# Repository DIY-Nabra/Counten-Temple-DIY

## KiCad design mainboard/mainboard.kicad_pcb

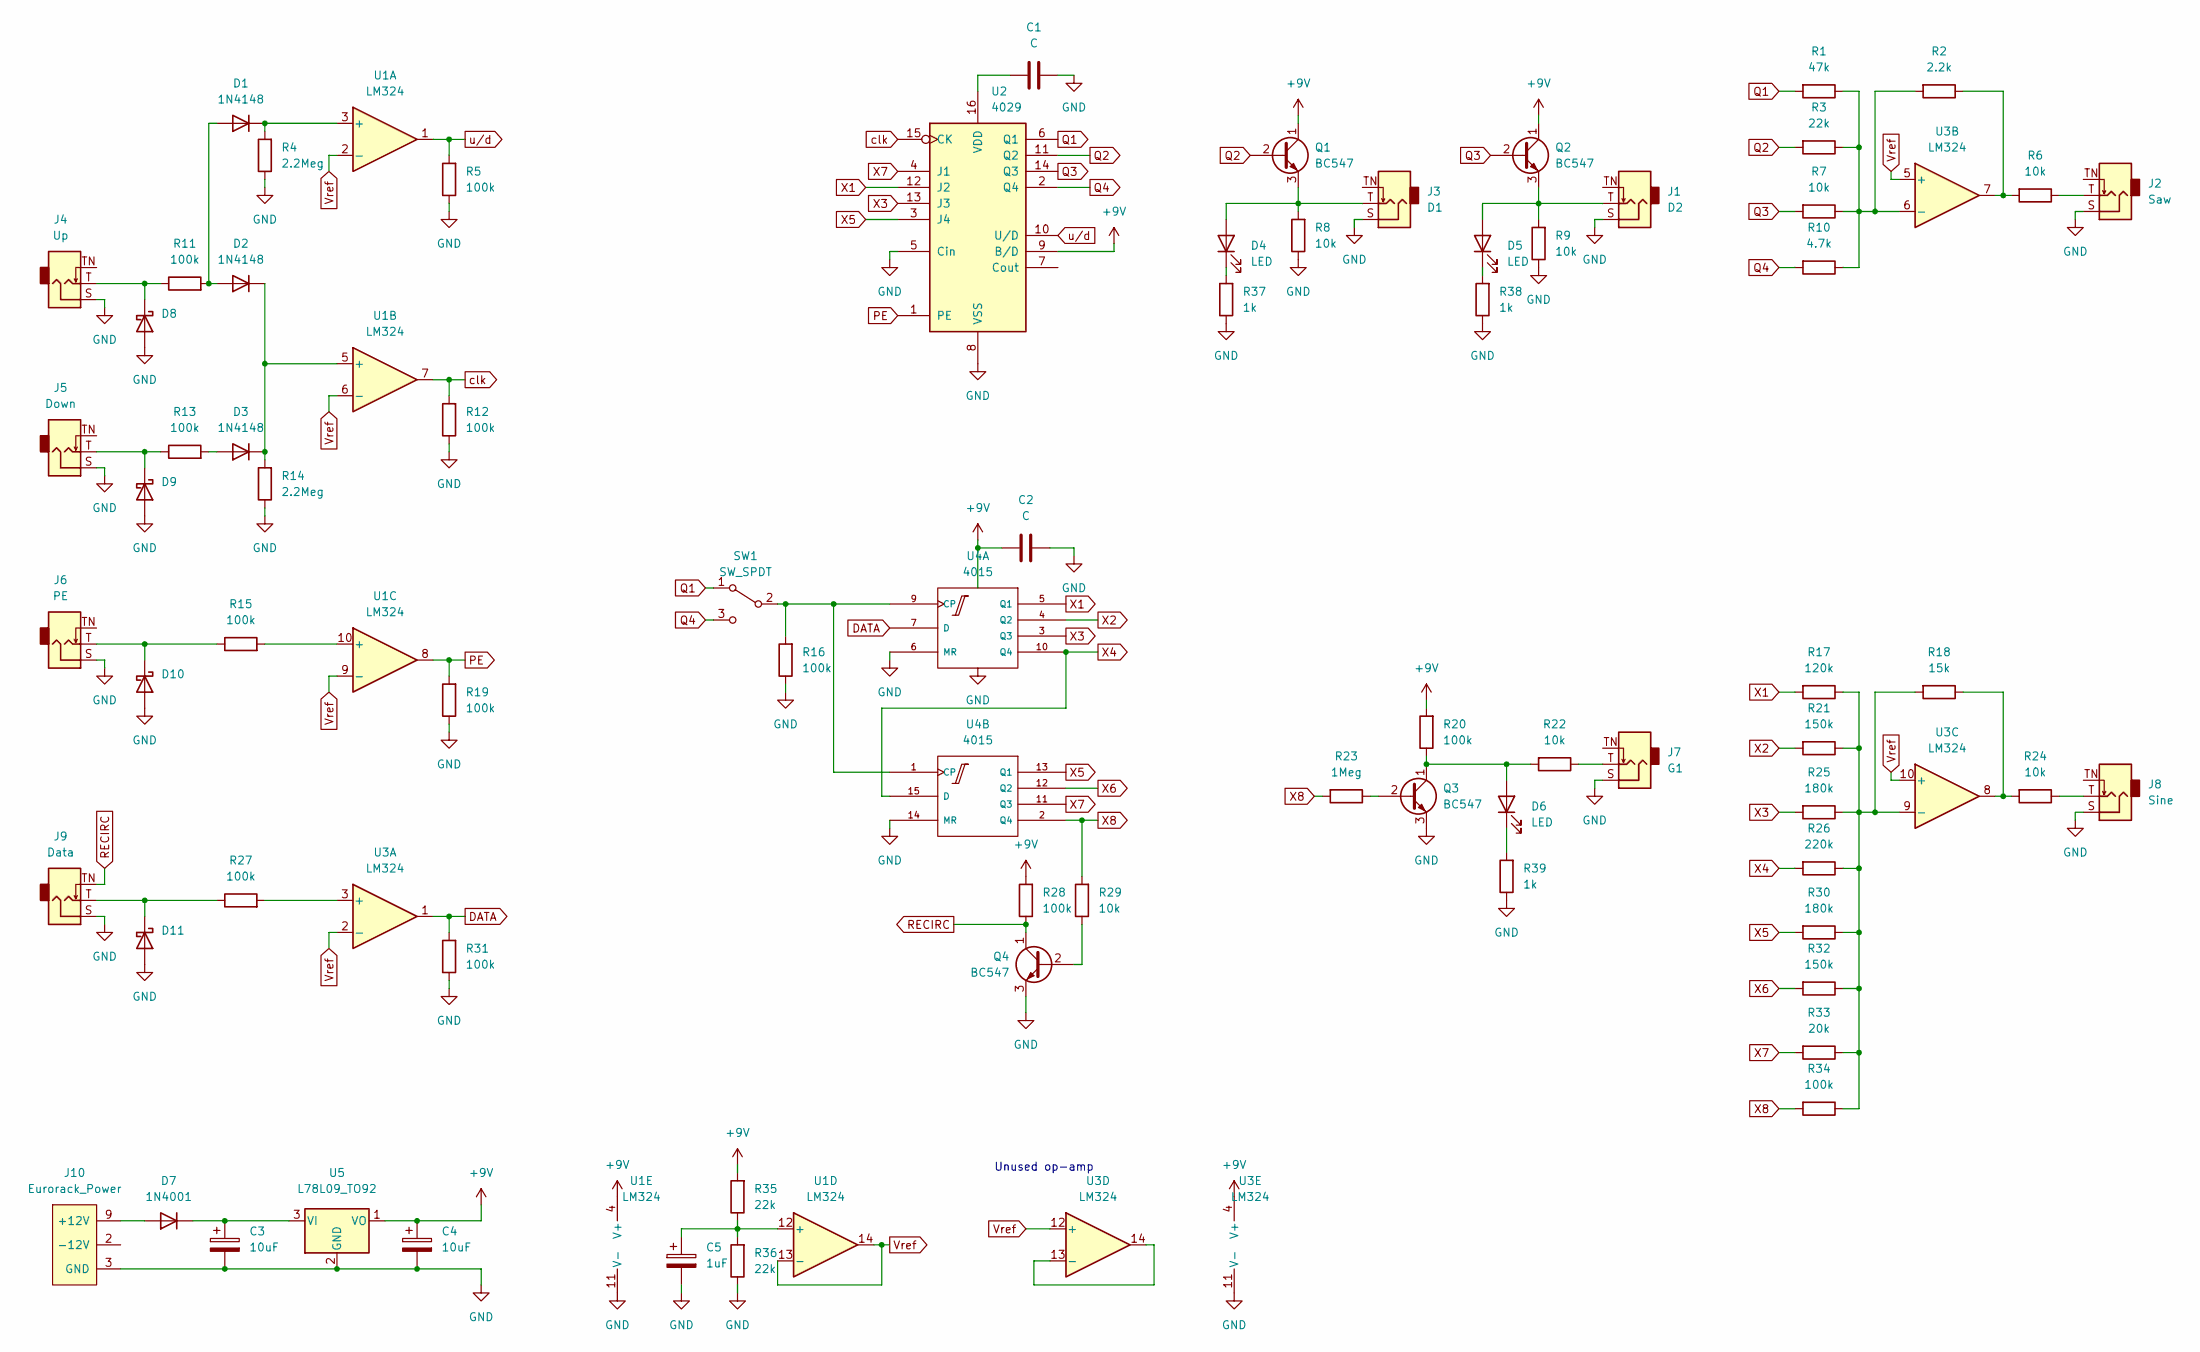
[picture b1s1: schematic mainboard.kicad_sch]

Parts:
C1, C2: C; C_Disc_D3.4mm_W2.1mm_P2.50mm
C3, C4: 10uF; CP_Radial_D6.3mm_P2.50mm
C5: 1uF; CP_Radial_D5.0mm_P2.50mm
D1, D2, D3: 1N4148; D_DO-35_SOD27_P7.62mm_Horizontal
D4, D5, D6: LED; LED_D3.0mm
D7: 1N4001; D_DO-41_SOD81_P10.16mm_Horizontal
D8, D9, D10, D11: (no value)
J1: D2; AudioJack_WQP518MA; MPN WQP-WQP518MA
J2: Saw; AudioJack_WQP518MA; MPN WQP-WQP518MA
J3: D1; AudioJack_WQP518MA; MPN WQP-WQP518MA
J4: Up; AudioJack_WQP518MA; MPN WQP-WQP518MA
J5: Down; AudioJack_WQP518MA; MPN WQP-WQP518MA
J6: PE; AudioJack_WQP518MA; MPN WQP-WQP518MA
J7: G1; AudioJack_WQP518MA; MPN WQP-WQP518MA
J8: Sine; AudioJack_WQP518MA; MPN WQP-WQP518MA
J9: Data; AudioJack_WQP518MA; MPN WQP-WQP518MA
J10: Eurorack_Power; Eurorack_Power_2x5_Shrouded; MPN 302-S101
Q1, Q2, Q3, Q4: BC547; TO-92_Inline
R1: 47k; R_Axial_DIN0204_L3.6mm_D1.6mm_P7.62mm_Horizontal
R2: 2.2k; R_Axial_DIN0204_L3.6mm_D1.6mm_P7.62mm_Horizontal
R3, R35, R36: 22k; R_Axial_DIN0204_L3.6mm_D1.6mm_P7.62mm_Horizontal
R4, R14: 2.2Meg; R_Axial_DIN0204_L3.6mm_D1.6mm_P7.62mm_Horizontal
R5, R11, R12, R13, R15, R16, R19, R20, R27, R28, R31, R34: 100k; R_Axial_DIN0204_L3.6mm_D1.6mm_P7.62mm_Horizontal
R6, R7, R8, R9, R22, R24, R29: 10k; R_Axial_DIN0204_L3.6mm_D1.6mm_P7.62mm_Horizontal
R10: 4.7k; R_Axial_DIN0204_L3.6mm_D1.6mm_P7.62mm_Horizontal
R17: 120k; R_Axial_DIN0204_L3.6mm_D1.6mm_P7.62mm_Horizontal
R18: 15k; R_Axial_DIN0204_L3.6mm_D1.6mm_P7.62mm_Horizontal
R21, R32: 150k; R_Axial_DIN0204_L3.6mm_D1.6mm_P7.62mm_Horizontal
R23: 1Meg; R_Axial_DIN0204_L3.6mm_D1.6mm_P7.62mm_Horizontal
R25, R30: 180k; R_Axial_DIN0204_L3.6mm_D1.6mm_P7.62mm_Horizontal
R26: 220k; R_Axial_DIN0204_L3.6mm_D1.6mm_P7.62mm_Horizontal
R33: 20k; R_Axial_DIN0204_L3.6mm_D1.6mm_P7.62mm_Horizontal
R37, R38, R39: 1k; R_Axial_DIN0204_L3.6mm_D1.6mm_P7.62mm_Horizontal
SW1: SW_SPDT; Miniature_Switch_SPDT_2.54MM
U1, U3: LM324; DIP-14_W7.62mm_Socket
U2: 4029; DIP-16_W7.62mm_Socket
U4: 4015; DIP-16_W7.62mm_Socket
U5: L78L09_TO92; TO-92_Inline

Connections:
+9V: C2.1, C4.1, Q1.1 (C), Q2.1 (C), R20.2, R28.2, R35.2, U1.4 (V+), U2.9 (B/D), U3.4 (V+), U4.16 (Vdd), U5.1 (VO)
DATA: R31.2, U3.1, U4.7 (D)
GND: C1.2, C2.2, C3.2, C4.2, C5.2, D8.2 (A), D9.2 (A), D10.2 (A), D11.2 (A), J1.S (Sleeve), J2.S (Sleeve), J3.S (Sleeve), J4.S (Sleeve), J5.S (Sleeve), J6.S (Sleeve), J7.S (Sleeve), J8.S (Sleeve), J9.S (Sleeve), J10.3 (GND), J10.4 (GND), J10.5 (GND), J10.6 (GND), J10.7 (GND), J10.8 (GND), Q3.3 (E), Q4.3 (E), R4.1, R5.1, R8.1, R9.1, R12.1, R14.1, R16.1, R19.1, R31.1, R36.1, R37.1, R38.1, R39.1, U1.11 (V-), U2.5 (Cin), U2.8 (VSS), U3.11 (V-), U4.6 (MR), U4.8 (Vss), U4.14 (MR), U5.2 (GND)
unnamed: C1.1, U2.16 (VDD)
unnamed: C3.1, D7.1 (K), U5.3 (VI)
unnamed: C5.1, R35.1, R36.2, U1.12 (+)
unnamed: D1.1 (K), R4.2, U1.3 (+)
unnamed: D1.2 (A), D2.2 (A), R11.2
unnamed: D2.1 (K), D3.1 (K), R14.2, U1.5 (+)
unnamed: D3.2 (A), R13.2
unnamed: D4.1 (K), R37.2
unnamed: D4.2 (A), J3.T (Tip), Q1.3 (E), R8.2
unnamed: D5.1 (K), R38.2
unnamed: D5.2 (A), J1.T (Tip), Q2.3 (E), R9.2
unnamed: D6.1 (K), R39.2
unnamed: D6.2 (A), Q3.1 (C), R20.1, R22.2
unnamed: D7.2 (A), J10.9 (+12V), J10.10 (+12V)
unnamed: J2.T (Tip), R6.1
unnamed: D8.1 (K), J4.T (Tip), R11.1
unnamed: D9.1 (K), J5.T (Tip), R13.1
unnamed: D10.1 (K), J6.T (Tip), R15.1
unnamed: J7.T (Tip), R22.1
unnamed: J8.T (Tip), R24.1
unnamed: D11.1 (K), J9.T (Tip), R27.1
unnamed: J10.1 (-12V), J10.2 (-12V)
unnamed: Q3.2 (B), R23.1
unnamed: Q4.2 (B), R29.1
unnamed: R1.1, R2.2, R3.1, R7.1, R10.1, U3.6 (-)
unnamed: R2.1, R6.2, U3.7
unnamed: R15.2, U1.10 (+)
unnamed: R16.2, SW1.2 (B), U4.1 (CP), U4.9 (CP)
unnamed: R17.1, R18.2, R21.1, R25.1, R26.1, R30.1, R32.1, R33.1, R34.1, U3.9 (-)
unnamed: R18.1, R24.2, U3.8
unnamed: R27.2, U3.3 (+)
unnamed: U3.13 (-), U3.14
PE: R19.2, U1.8, U2.1 (PE)
Q1: R1.2, SW1.1 (A), U2.6 (Q1)
Q2: Q1.2 (B), R3.2, U2.11 (Q2)
Q3: Q2.2 (B), R7.2, U2.14 (Q3)
Q4: R10.2, SW1.3 (C), U2.2 (Q4)
RECIRC: J9.TN (Tip_normalize), Q4.1 (C), R28.1
Vref: U1.2 (-), U1.6 (-), U1.9 (-), U1.13 (-), U1.14, U3.2 (-), U3.5 (+), U3.10 (+), U3.12 (+)
X1: R17.2, U2.12 (J2), U4.5 (Q1)
X2: R21.2, U4.4 (Q2)
X3: R25.2, U2.13 (J3), U4.3 (Q3)
X4: R26.2, U4.10 (Q4), U4.15 (D)
X5: R30.2, U2.3 (J4), U4.13 (Q1)
X6: R32.2, U4.12 (Q2)
X7: R33.2, U2.4 (J1), U4.11 (Q3)
X8: R23.2, R29.2, R34.2, U4.2 (Q4)
clk: R12.2, U1.7, U2.15 (CK)
u/d: R5.2, U1.1, U2.10 (U/D)

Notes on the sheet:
Unused op-amp

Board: 2 copper layers, 75 parts (10 on the bottom side), 52 nets, no tracks yet.
